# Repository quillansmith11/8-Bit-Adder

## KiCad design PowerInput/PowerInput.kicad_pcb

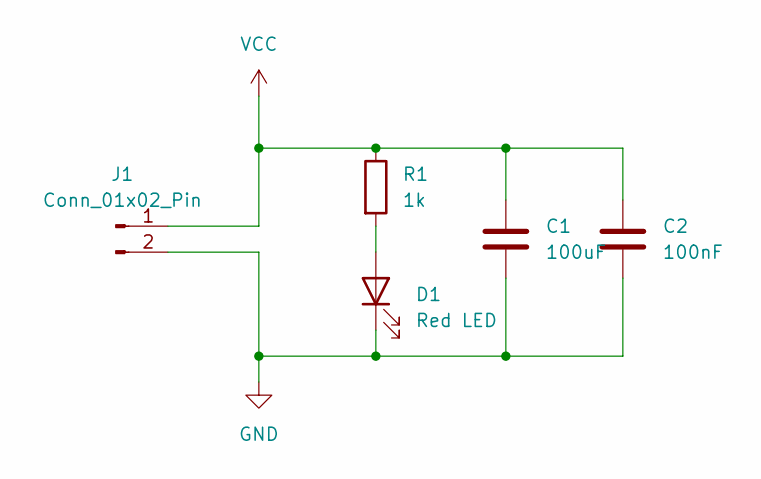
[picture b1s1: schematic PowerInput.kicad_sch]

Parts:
C1: 100uF; CP_Elec_10x10.5
C2: 100nF; C_0805_2012Metric
D1: Red LED; LED_0805_2012Metric
J1: Conn_01x02_Pin; BarrelJack_Kycon_KLDX-0202-xC_Horizontal
R1: 1k; R_0805_2012Metric

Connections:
GND: C1.2, C2.2, D1.1 (K), J1.2
unnamed: D1.2 (A), R1.2
VCC: C1.1, C2.1, J1.1, R1.1

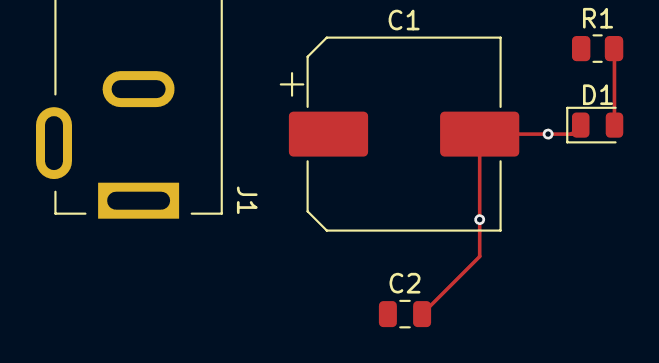
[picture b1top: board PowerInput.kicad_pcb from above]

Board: 2 copper layers, 5 parts (0 on the bottom side), 3 nets.

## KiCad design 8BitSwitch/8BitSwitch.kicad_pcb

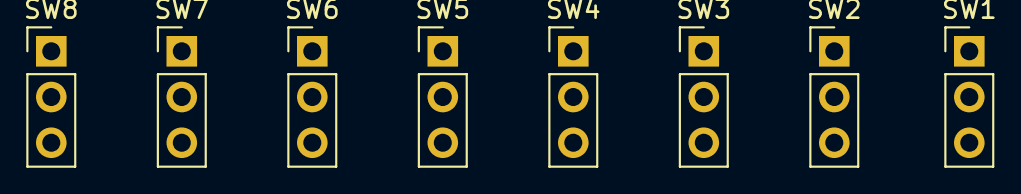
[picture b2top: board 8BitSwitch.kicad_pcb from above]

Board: 2 copper layers, 8 parts (0 on the bottom side), 2 nets, no tracks yet.

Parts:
SW1, SW2, SW3, SW4, SW5, SW6, SW7, SW8: SW_Nidec_CAS-120A1; PinHeader_1x03_P2.54mm_Vertical

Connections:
GND: SW1.3 (A), SW2.3 (A), SW3.3 (A), SW4.3 (A), SW5.3 (A), SW6.3 (A), SW7.3 (A), SW8.3 (A)
VCC: SW1.1 (C), SW2.1 (C), SW3.1 (C), SW4.1 (C), SW5.1 (C), SW6.1 (C), SW7.1 (C), SW8.1 (C)

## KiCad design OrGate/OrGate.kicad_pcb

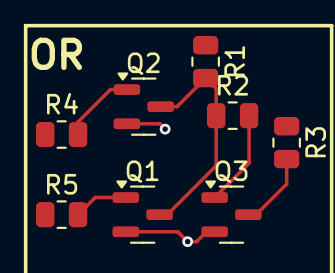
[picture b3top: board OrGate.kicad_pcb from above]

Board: 2 copper layers, 8 parts (0 on the bottom side), 7 nets.

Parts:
Q1, Q2, Q3: NPN Transistor; SOT-23
R1, R3: 2.7k; R_0805_2012Metric
R2: 39k; R_0805_2012Metric
R4, R5: 42k; R_0805_2012Metric

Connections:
/OUT: Q3.3 (C), R3.2
GND: Q1.2 (E), Q2.2 (E), Q3.2 (E)
unnamed: Q1.3 (C), Q2.3 (C), R1.2, R2.1
unnamed: Q1.1 (B), R5.2
unnamed: Q2.1 (B), R4.2
unnamed: Q3.1 (B), R2.2
VCC: R1.1, R3.1

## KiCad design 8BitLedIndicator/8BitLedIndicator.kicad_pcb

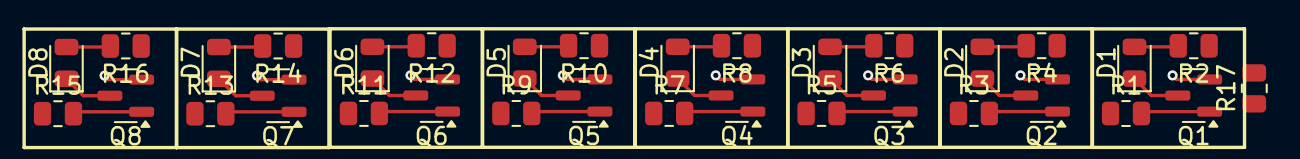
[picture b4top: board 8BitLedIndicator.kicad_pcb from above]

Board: 2 copper layers, 33 parts (0 on the bottom side), 26 nets.

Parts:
D1, D2, D3, D4, D5, D6, D7, D8: Red LED; LED_0805_2012Metric
Q1, Q2, Q3, Q4, Q5, Q6, Q7, Q8: NPN Transistor; SOT-23
R1, R3, R5, R7, R9, R11, R13, R15: 42k; R_0805_2012Metric
R2, R4, R6, R8, R10, R12, R14, R16: 200; R_0805_2012Metric
R17: R; R_0805_2012Metric

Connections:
GND: Q1.2 (E), Q2.2 (E), Q3.2 (E), Q4.2 (E), Q5.2 (E), Q6.2 (E), Q7.2 (E), Q8.2 (E)
unnamed: D1.2 (A), R2.2
unnamed: D1.1 (K), Q1.3 (C)
unnamed: D2.2 (A), R4.2
unnamed: D2.1 (K), Q2.3 (C)
unnamed: D3.2 (A), R6.2
unnamed: D3.1 (K), Q3.3 (C)
unnamed: D4.2 (A), R8.2
unnamed: D4.1 (K), Q4.3 (C)
unnamed: D5.2 (A), R10.2
unnamed: D5.1 (K), Q5.3 (C)
unnamed: D6.2 (A), R12.2
unnamed: D6.1 (K), Q6.3 (C)
unnamed: D7.2 (A), R14.2
unnamed: D7.1 (K), Q7.3 (C)
unnamed: D8.2 (A), R16.2
unnamed: D8.1 (K), Q8.3 (C)
unnamed: Q1.1 (B), R1.2
unnamed: Q2.1 (B), R3.2
unnamed: Q3.1 (B), R5.2
unnamed: Q4.1 (B), R7.2
unnamed: Q5.1 (B), R9.2
unnamed: Q6.1 (B), R11.2
unnamed: Q7.1 (B), R13.2
unnamed: Q8.1 (B), R15.2
VCC: R2.1, R4.1, R6.1, R8.1, R10.1, R12.1, R14.1, R16.1

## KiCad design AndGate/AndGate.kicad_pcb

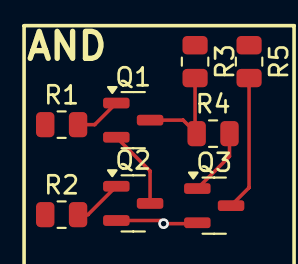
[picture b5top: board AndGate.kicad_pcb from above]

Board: 2 copper layers, 8 parts (0 on the bottom side), 8 nets.

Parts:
Q1, Q2, Q3: NPN Transistor; SOT-23
R1, R2: 42k; R_0805_2012Metric
R3: 2.1k; R_0805_2012Metric
R4: 39k; R_0805_2012Metric
R5: 2.7k; R_0805_2012Metric

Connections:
/OUT: Q3.3 (C), R5.2
GND: Q2.2 (E), Q3.2 (E)
unnamed: Q1.1 (B), R1.2
unnamed: Q1.3 (C), R3.2, R4.1
unnamed: Q1.2 (E), Q2.3 (C)
unnamed: Q2.1 (B), R2.2
unnamed: Q3.1 (B), R4.2
VCC: R3.1, R5.1

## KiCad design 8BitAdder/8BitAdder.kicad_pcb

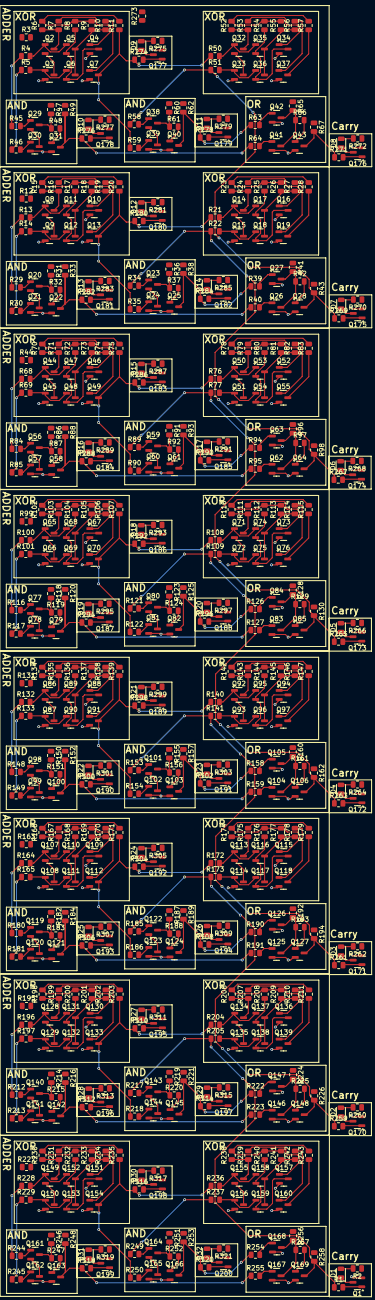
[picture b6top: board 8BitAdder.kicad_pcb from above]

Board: 2 copper layers, 553 parts (0 on the bottom side), 395 nets.

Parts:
D1, D2, D3, D4, D5, D6, D7, D8, D9, D10, D11, D12, D13, D14, D15, D16, D17, D18, D19, D20, D21, D22, D23, D24, D25, D26, D27, D28, D29, D30, D31, D32: Red LED; LED_0805_2012Metric
Q1, Q2, Q3, Q4, Q5, Q6, Q7, Q8, Q9, Q10, Q11, Q12, Q13, Q14, Q15, Q16, Q17, Q18, Q19, Q20, Q21, Q22, Q23, Q24, Q25, Q26, Q27, Q28, Q29, Q30, Q31, Q32, Q33, Q34, Q35, Q36, Q37, Q38, Q39, Q40, Q41, Q42, Q43, Q44, Q45, Q46, Q47, Q48, Q49, Q50, Q51, Q52, Q53, Q54, Q55, Q56, Q57, Q58, Q59, Q60, Q61, Q62, Q63, Q64, Q65, Q66, Q67, Q68, Q69, Q70, Q71, Q72, Q73, Q74, Q75, Q76, Q77, Q78, Q79, Q80, Q81, Q82, Q83, Q84, Q85, Q86, Q87, Q88, Q89, Q90, Q91, Q92, Q93, Q94, Q95, Q96, Q97, Q98, Q99, Q100, Q101, Q102, Q103, Q104, Q105, Q106, Q107, Q108, Q109, Q110, Q111, Q112, Q113, Q114, Q115, Q116, Q117, Q118, Q119, Q120, Q121, Q122, Q123, Q124, Q125, Q126, Q127, Q128, Q129, Q130, Q131, Q132, Q133, Q134, Q135, Q136, Q137, Q138, Q139, Q140, Q141, Q142, Q143, Q144, Q145, Q146, Q147, Q148, Q149, Q150, Q151, Q152, Q153, Q154, Q155, Q156, Q157, Q158, Q159, Q160, Q161, Q162, Q163, Q164, Q165, Q166, Q167, Q168, Q169, Q170, Q171, Q172, Q173, Q174, Q175, Q176, Q177, Q178, Q179, Q180, Q181, Q182, Q183, Q184, Q185, Q186, Q187, Q188, Q189, Q190, Q191, Q192, Q193, Q194, Q195, Q196, Q197, Q198, Q199, Q200: NPN Transistor; SOT-23
R1, R29, R30, R34, R35, R39, R40, R45, R46, R58, R59, R63, R64, R84, R85, R89, R90, R94, R95, R116, R117, R121, R122, R126, R127, R148, R149, R153, R154, R158, R159, R180, R181, R185, R186, R190, R191, R212, R213, R217, R218, R222, R223, R244, R245, R249, R250, R254, R255, R259, R261, R263, R265, R267, R269, R271, R274, R276, R278, R280, R282, R284, R286, R288, R290, R292, R294, R296, R298, R300, R302, R304, R306, R308, R310, R312, R314, R316, R318, R320: 42k; R_0805_2012Metric
R2, R260, R262, R264, R266, R268, R270, R272, R275, R277, R279, R281, R283, R285, R287, R289, R291, R293, R295, R297, R299, R301, R303, R305, R307, R309, R311, R313, R315, R317, R319, R321: 200; R_0805_2012Metric
R3, R12, R44, R99, R131, R163, R195, R227, R273: R; R_0805_2012Metric
R4, R5, R7, R13, R14, R16, R21, R22, R24, R50, R51, R53, R68, R69, R71, R76, R77, R79, R100, R101, R103, R108, R109, R111, R132, R133, R135, R140, R141, R143, R164, R165, R167, R172, R173, R175, R196, R197, R199, R204, R205, R207, R228, R229, R231, R236, R237, R239: 1k; R_0805_2012Metric
R6, R9, R15, R18, R23, R26, R31, R36, R47, R52, R55, R60, R70, R73, R78, R81, R86, R91, R102, R105, R110, R113, R118, R123, R134, R137, R142, R145, R150, R155, R166, R169, R174, R177, R182, R187, R198, R201, R206, R209, R214, R219, R230, R233, R238, R241, R246, R251: 2.1k; R_0805_2012Metric
R8, R11, R17, R20, R25, R28, R33, R38, R41, R43, R49, R54, R57, R62, R65, R67, R72, R75, R80, R83, R88, R93, R96, R98, R104, R107, R112, R115, R120, R125, R128, R130, R136, R139, R144, R147, R152, R157, R160, R162, R168, R171, R176, R179, R184, R189, R192, R194, R200, R203, R208, R211, R216, R221, R224, R226, R232, R235, R240, R243, R248, R253, R256, R258: 2.7k; R_0805_2012Metric
R10, R19, R27, R32, R37, R42, R48, R56, R61, R66, R74, R82, R87, R92, R97, R106, R114, R119, R124, R129, R138, R146, R151, R156, R161, R170, R178, R183, R188, R193, R202, R210, R215, R220, R225, R234, R242, R247, R252, R257: 39k; R_0805_2012Metric

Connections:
/A0: R228.1, R244.1
/A1: R196.1, R212.1
/A2: R164.1, R180.1
/A3: R132.1, R148.1
/A4: R100.1, R116.1
/A5: R68.1, R84.1
/A6: R13.1, R29.1
/A7: R4.1, R45.1
/Adder0/And Gate2/B: Q154.3 (C), R235.1, R236.1, R250.1, R316.1
/Adder0/And Gate2/OUT: Q166.3 (C), R253.2, R254.1, R320.1
/Adder0/And Gate3/OUT: Q163.3 (C), R248.2, R255.1, R318.1
/Adder0/XorGate1/Asig: Q155.1 (B), Q158.1 (B), R236.2
/Adder0/XorGate1/Bsig: Q156.1 (B), Q159.1 (B), R237.2
/Adder0/XorGate2/Asig: Q149.1 (B), Q152.1 (B), R228.2
/Adder0/XorGate2/Bsig: Q150.1 (B), Q153.1 (B), R229.2
/Adder1/And Gate2/B: Q133.3 (C), R203.1, R204.1, R218.1, R310.1
/Adder1/And Gate2/OUT: Q145.3 (C), R221.2, R222.1, R314.1
/Adder1/And Gate3/OUT: Q142.3 (C), R216.2, R223.1, R312.1
/Adder1/XorGate1/Asig: Q134.1 (B), Q137.1 (B), R204.2
/Adder1/XorGate1/Bsig: Q135.1 (B), Q138.1 (B), R205.2
/Adder1/XorGate2/Asig: Q128.1 (B), Q131.1 (B), R196.2
/Adder1/XorGate2/Bsig: Q129.1 (B), Q132.1 (B), R197.2
/Adder2/And Gate2/B: Q112.3 (C), R171.1, R172.1, R186.1, R304.1
/Adder2/And Gate2/OUT: Q124.3 (C), R189.2, R190.1, R308.1
/Adder2/And Gate3/OUT: Q121.3 (C), R184.2, R191.1, R306.1
/Adder2/XorGate1/Asig: Q113.1 (B), Q116.1 (B), R172.2
/Adder2/XorGate1/Bsig: Q114.1 (B), Q117.1 (B), R173.2
/Adder2/XorGate2/Asig: Q107.1 (B), Q110.1 (B), R164.2
/Adder2/XorGate2/Bsig: Q108.1 (B), Q111.1 (B), R165.2
/Adder3/And Gate2/B: Q91.3 (C), R139.1, R140.1, R154.1, R298.1
/Adder3/And Gate2/OUT: Q103.3 (C), R157.2, R158.1, R302.1
/Adder3/And Gate3/OUT: Q100.3 (C), R152.2, R159.1, R300.1
/Adder3/XorGate1/Asig: Q92.1 (B), Q95.1 (B), R140.2
/Adder3/XorGate1/Bsig: Q93.1 (B), Q96.1 (B), R141.2
/Adder3/XorGate2/Asig: Q86.1 (B), Q89.1 (B), R132.2
/Adder3/XorGate2/Bsig: Q87.1 (B), Q90.1 (B), R133.2
/Adder4/And Gate2/B: Q70.3 (C), R107.1, R108.1, R122.1, R292.1
/Adder4/And Gate2/OUT: Q82.3 (C), R125.2, R126.1, R296.1
/Adder4/And Gate3/OUT: Q79.3 (C), R120.2, R127.1, R294.1
/Adder4/Cout: Q85.3 (C), R77.1, R89.1, R130.2, R265.1
/Adder4/XorGate1/Asig: Q71.1 (B), Q74.1 (B), R108.2
/Adder4/XorGate1/Bsig: Q72.1 (B), Q75.1 (B), R109.2
/Adder4/XorGate2/Asig: Q65.1 (B), Q68.1 (B), R100.2
/Adder4/XorGate2/Bsig: Q66.1 (B), Q69.1 (B), R101.2
/Adder5/And Gate2/B: Q49.3 (C), R75.1, R76.1, R90.1, R286.1
/Adder5/And Gate2/OUT: Q61.3 (C), R93.2, R94.1, R290.1
/Adder5/And Gate3/OUT: Q58.3 (C), R88.2, R95.1, R288.1
/Adder5/XorGate1/Asig: Q50.1 (B), Q53.1 (B), R76.2
/Adder5/XorGate1/Bsig: Q51.1 (B), Q54.1 (B), R77.2
/Adder5/XorGate2/Asig: Q44.1 (B), Q47.1 (B), R68.2
/Adder5/XorGate2/Bsig: Q45.1 (B), Q48.1 (B), R69.2
/Adder6/And Gate2/B: Q13.3 (C), R20.1, R21.1, R35.1, R280.1
/Adder6/And Gate2/OUT: Q25.3 (C), R38.2, R39.1, R284.1
/Adder6/And Gate3/OUT: Q22.3 (C), R33.2, R40.1, R282.1
/Adder6/XorGate1/Asig: Q14.1 (B), Q17.1 (B), R21.2
/Adder6/XorGate1/Bsig: Q15.1 (B), Q18.1 (B), R22.2
/Adder6/XorGate2/Asig: Q8.1 (B), Q11.1 (B), R13.2
/Adder6/XorGate2/Bsig: Q9.1 (B), Q12.1 (B), R14.2
/Adder7/And Gate2/B: Q7.3 (C), R11.1, R50.1, R59.1, R274.1
/Adder7/And Gate2/OUT: Q40.3 (C), R62.2, R63.1, R278.1
/Adder7/And Gate3/OUT: Q31.3 (C), R49.2, R64.1, R276.1
/Adder7/XorGate1/Asig: Q32.1 (B), Q35.1 (B), R50.2
/Adder7/XorGate1/Bsig: Q33.1 (B), Q36.1 (B), R51.2
/Adder7/XorGate2/Asig: Q2.1 (B), Q5.1 (B), R4.2
/Adder7/XorGate2/Bsig: Q3.1 (B), Q6.1 (B), R5.2
/B0: R229.1, R245.1
/B1: R197.1, R213.1
/B2: R165.1, R181.1
/B3: R133.1, R149.1
/B4: R101.1, R117.1
/B5: R69.1, R85.1
/B6: R14.1, R30.1
/B7: R5.1, R46.1
/Cin: R237.1, R249.1
/Cout0: Q169.3 (C), R1.1, R205.1, R217.1, R258.2
/Cout1: Q148.3 (C), R173.1, R185.1, R226.2, R259.1
/Cout2: Q127.3 (C), R141.1, R153.1, R194.2, R261.1
/Cout3: Q106.3 (C), R109.1, R121.1, R162.2, R263.1
/Cout5: Q64.3 (C), R22.1, R34.1, R98.2, R267.1
/Cout6: Q28.3 (C), R43.2, R51.1, R58.1, R269.1
/Cout7: Q43.3 (C), R67.2, R271.1
/SUM0: Q160.3 (C), R243.1
/SUM1: Q139.3 (C), R211.1
/SUM2: Q118.3 (C), R179.1
/SUM3: Q97.3 (C), R147.1
/SUM4: Q76.3 (C), R115.1
/SUM5: Q55.3 (C), R83.1
/SUM6: Q19.3 (C), R28.1
/SUM7: Q37.3 (C), R57.1
GND: Q1.2 (E), Q3.2 (E), Q4.2 (E), Q7.2 (E), Q9.2 (E), Q10.2 (E), Q13.2 (E), Q15.2 (E), Q16.2 (E), Q19.2 (E), Q21.2 (E), Q22.2 (E), Q24.2 (E), Q25.2 (E), Q26.2 (E), Q27.2 (E), Q28.2 (E), Q30.2 (E), Q31.2 (E), Q33.2 (E), Q34.2 (E), Q37.2 (E), Q39.2 (E), Q40.2 (E), Q41.2 (E), Q42.2 (E), Q43.2 (E), Q45.2 (E), Q46.2 (E), Q49.2 (E), Q51.2 (E), Q52.2 (E), Q55.2 (E), Q57.2 (E), Q58.2 (E), Q60.2 (E), Q61.2 (E), Q62.2 (E), Q63.2 (E), Q64.2 (E), Q66.2 (E), Q67.2 (E), Q70.2 (E), Q72.2 (E), Q73.2 (E), Q76.2 (E), Q78.2 (E), Q79.2 (E), Q81.2 (E), Q82.2 (E), Q83.2 (E), Q84.2 (E), Q85.2 (E), Q87.2 (E), Q88.2 (E), Q91.2 (E), Q93.2 (E), Q94.2 (E), Q97.2 (E), Q99.2 (E), Q100.2 (E), Q102.2 (E), Q103.2 (E), Q104.2 (E), Q105.2 (E), Q106.2 (E), Q108.2 (E), Q109.2 (E), Q112.2 (E), Q114.2 (E), Q115.2 (E), Q118.2 (E), Q120.2 (E), Q121.2 (E), Q123.2 (E), Q124.2 (E), Q125.2 (E), Q126.2 (E), Q127.2 (E), Q129.2 (E), Q130.2 (E), Q133.2 (E), Q135.2 (E), Q136.2 (E), Q139.2 (E), Q141.2 (E), Q142.2 (E), Q144.2 (E), Q145.2 (E), Q146.2 (E), Q147.2 (E), Q148.2 (E), Q150.2 (E), Q151.2 (E), Q154.2 (E), Q156.2 (E), Q157.2 (E), Q160.2 (E), Q162.2 (E), Q163.2 (E), Q165.2 (E), Q166.2 (E), Q167.2 (E), Q168.2 (E), Q169.2 (E), Q170.2 (E), Q171.2 (E), Q172.2 (E), Q173.2 (E), Q174.2 (E), Q175.2 (E), Q176.2 (E), Q177.2 (E), Q178.2 (E), Q179.2 (E), Q180.2 (E), Q181.2 (E), Q182.2 (E), Q183.2 (E), Q184.2 (E), Q185.2 (E), Q186.2 (E), Q187.2 (E), Q188.2 (E), Q189.2 (E), Q190.2 (E), Q191.2 (E), Q192.2 (E), Q193.2 (E), Q194.2 (E), Q195.2 (E), Q196.2 (E), Q197.2 (E), Q198.2 (E), Q199.2 (E), Q200.2 (E)
unnamed: D1.2 (A), R2.2
unnamed: D1.1 (K), Q1.3 (C)
unnamed: D2.2 (A), R260.2
unnamed: D2.1 (K), Q170.3 (C)
unnamed: D3.2 (A), R262.2
unnamed: D3.1 (K), Q171.3 (C)
unnamed: D4.2 (A), R264.2
unnamed: D4.1 (K), Q172.3 (C)
unnamed: D5.2 (A), R266.2
unnamed: D5.1 (K), Q173.3 (C)
unnamed: D6.2 (A), R268.2
unnamed: D6.1 (K), Q174.3 (C)
unnamed: D7.2 (A), R270.2
unnamed: D7.1 (K), Q175.3 (C)
unnamed: D8.2 (A), R272.2
unnamed: D8.1 (K), Q176.3 (C)
unnamed: D9.2 (A), R275.2
unnamed: D9.1 (K), Q177.3 (C)
unnamed: D10.2 (A), R277.2
unnamed: D10.1 (K), Q178.3 (C)
unnamed: D11.2 (A), R279.2
unnamed: D11.1 (K), Q179.3 (C)
unnamed: D12.2 (A), R281.2
unnamed: D12.1 (K), Q180.3 (C)
unnamed: D13.2 (A), R283.2
unnamed: D13.1 (K), Q181.3 (C)
unnamed: D14.2 (A), R285.2
unnamed: D14.1 (K), Q182.3 (C)
unnamed: D15.2 (A), R287.2
unnamed: D15.1 (K), Q183.3 (C)
unnamed: D16.2 (A), R289.2
unnamed: D16.1 (K), Q184.3 (C)
unnamed: D17.2 (A), R291.2
unnamed: D17.1 (K), Q185.3 (C)
unnamed: D18.2 (A), R293.2
unnamed: D18.1 (K), Q186.3 (C)
unnamed: D19.2 (A), R295.2
unnamed: D19.1 (K), Q187.3 (C)
unnamed: D20.2 (A), R297.2
unnamed: D20.1 (K), Q188.3 (C)
unnamed: D21.2 (A), R299.2
unnamed: D21.1 (K), Q189.3 (C)
unnamed: D22.2 (A), R301.2
unnamed: D22.1 (K), Q190.3 (C)
unnamed: D23.2 (A), R303.2
unnamed: D23.1 (K), Q191.3 (C)
unnamed: D24.2 (A), R305.2
unnamed: D24.1 (K), Q192.3 (C)
unnamed: D25.2 (A), R307.2
unnamed: D25.1 (K), Q193.3 (C)
unnamed: D26.2 (A), R309.2
unnamed: D26.1 (K), Q194.3 (C)
unnamed: D27.2 (A), R311.2
unnamed: D27.1 (K), Q195.3 (C)
unnamed: D28.2 (A), R313.2
unnamed: D28.1 (K), Q196.3 (C)
unnamed: D29.2 (A), R315.2
unnamed: D29.1 (K), Q197.3 (C)
unnamed: D30.2 (A), R317.2
unnamed: D30.1 (K), Q198.3 (C)
unnamed: D31.2 (A), R319.2
unnamed: D31.1 (K), Q199.3 (C)
unnamed: D32.2 (A), R321.2
unnamed: D32.1 (K), Q200.3 (C)
unnamed: Q1.1 (B), R1.2
unnamed: Q2.3 (C), R6.1, R7.1
unnamed: Q2.2 (E), Q3.3 (C)
unnamed: Q4.1 (B), R7.2
unnamed: Q4.3 (C), Q5.2 (E), Q6.2 (E), R8.1
unnamed: Q5.3 (C), Q6.3 (C), R9.1, R10.1
unnamed: Q7.1 (B), R10.2
unnamed: Q8.3 (C), R15.1, R16.1
unnamed: Q8.2 (E), Q9.3 (C)
unnamed: Q10.1 (B), R16.2
unnamed: Q10.3 (C), Q11.2 (E), Q12.2 (E), R17.1
unnamed: Q11.3 (C), Q12.3 (C), R18.1, R19.1
unnamed: Q13.1 (B), R19.2
unnamed: Q14.3 (C), R23.1, R24.1
unnamed: Q14.2 (E), Q15.3 (C)
unnamed: Q16.1 (B), R24.2
unnamed: Q16.3 (C), Q17.2 (E), Q18.2 (E), R25.1
unnamed: Q17.3 (C), Q18.3 (C), R26.1, R27.1
unnamed: Q19.1 (B), R27.2
unnamed: Q20.1 (B), R29.2
unnamed: Q20.3 (C), R31.2, R32.1
unnamed: Q20.2 (E), Q21.3 (C)
unnamed: Q21.1 (B), R30.2
unnamed: Q22.1 (B), R32.2
unnamed: Q23.1 (B), R34.2
unnamed: Q23.3 (C), R36.2, R37.1
unnamed: Q23.2 (E), Q24.3 (C)
unnamed: Q24.1 (B), R35.2
unnamed: Q25.1 (B), R37.2
unnamed: Q26.1 (B), R40.2
unnamed: Q26.3 (C), Q27.3 (C), R41.2, R42.1
unnamed: Q27.1 (B), R39.2
unnamed: Q28.1 (B), R42.2
unnamed: Q29.1 (B), R45.2
unnamed: Q29.3 (C), R47.2, R48.1
unnamed: Q29.2 (E), Q30.3 (C)
unnamed: Q30.1 (B), R46.2
unnamed: Q31.1 (B), R48.2
unnamed: Q32.3 (C), R52.1, R53.1
unnamed: Q32.2 (E), Q33.3 (C)
unnamed: Q34.1 (B), R53.2
unnamed: Q34.3 (C), Q35.2 (E), Q36.2 (E), R54.1
unnamed: Q35.3 (C), Q36.3 (C), R55.1, R56.1
unnamed: Q37.1 (B), R56.2
unnamed: Q38.1 (B), R58.2
unnamed: Q38.3 (C), R60.2, R61.1
unnamed: Q38.2 (E), Q39.3 (C)
unnamed: Q39.1 (B), R59.2
unnamed: Q40.1 (B), R61.2
unnamed: Q41.1 (B), R64.2
unnamed: Q41.3 (C), Q42.3 (C), R65.2, R66.1
unnamed: Q42.1 (B), R63.2
unnamed: Q43.1 (B), R66.2
unnamed: Q44.3 (C), R70.1, R71.1
unnamed: Q44.2 (E), Q45.3 (C)
unnamed: Q46.1 (B), R71.2
unnamed: Q46.3 (C), Q47.2 (E), Q48.2 (E), R72.1
unnamed: Q47.3 (C), Q48.3 (C), R73.1, R74.1
unnamed: Q49.1 (B), R74.2
unnamed: Q50.3 (C), R78.1, R79.1
unnamed: Q50.2 (E), Q51.3 (C)
unnamed: Q52.1 (B), R79.2
unnamed: Q52.3 (C), Q53.2 (E), Q54.2 (E), R80.1
unnamed: Q53.3 (C), Q54.3 (C), R81.1, R82.1
unnamed: Q55.1 (B), R82.2
unnamed: Q56.1 (B), R84.2
unnamed: Q56.3 (C), R86.2, R87.1
unnamed: Q56.2 (E), Q57.3 (C)
unnamed: Q57.1 (B), R85.2
unnamed: Q58.1 (B), R87.2
unnamed: Q59.1 (B), R89.2
unnamed: Q59.3 (C), R91.2, R92.1
unnamed: Q59.2 (E), Q60.3 (C)
unnamed: Q60.1 (B), R90.2
unnamed: Q61.1 (B), R92.2
unnamed: Q62.1 (B), R95.2
unnamed: Q62.3 (C), Q63.3 (C), R96.2, R97.1
unnamed: Q63.1 (B), R94.2
unnamed: Q64.1 (B), R97.2
unnamed: Q65.3 (C), R102.1, R103.1
unnamed: Q65.2 (E), Q66.3 (C)
unnamed: Q67.1 (B), R103.2
unnamed: Q67.3 (C), Q68.2 (E), Q69.2 (E), R104.1
unnamed: Q68.3 (C), Q69.3 (C), R105.1, R106.1
unnamed: Q70.1 (B), R106.2
unnamed: Q71.3 (C), R110.1, R111.1
unnamed: Q71.2 (E), Q72.3 (C)
unnamed: Q73.1 (B), R111.2
unnamed: Q73.3 (C), Q74.2 (E), Q75.2 (E), R112.1
unnamed: Q74.3 (C), Q75.3 (C), R113.1, R114.1
unnamed: Q76.1 (B), R114.2
unnamed: Q77.1 (B), R116.2
unnamed: Q77.3 (C), R118.2, R119.1
unnamed: Q77.2 (E), Q78.3 (C)
unnamed: Q78.1 (B), R117.2
unnamed: Q79.1 (B), R119.2
unnamed: Q80.1 (B), R121.2
unnamed: Q80.3 (C), R123.2, R124.1
unnamed: Q80.2 (E), Q81.3 (C)
unnamed: Q81.1 (B), R122.2
unnamed: Q82.1 (B), R124.2
unnamed: Q83.1 (B), R127.2
unnamed: Q83.3 (C), Q84.3 (C), R128.2, R129.1
unnamed: Q84.1 (B), R126.2
unnamed: Q85.1 (B), R129.2
unnamed: Q86.3 (C), R134.1, R135.1
unnamed: Q86.2 (E), Q87.3 (C)
unnamed: Q88.1 (B), R135.2
unnamed: Q88.3 (C), Q89.2 (E), Q90.2 (E), R136.1
unnamed: Q89.3 (C), Q90.3 (C), R137.1, R138.1
unnamed: Q91.1 (B), R138.2
unnamed: Q92.3 (C), R142.1, R143.1
unnamed: Q92.2 (E), Q93.3 (C)
unnamed: Q94.1 (B), R143.2
unnamed: Q94.3 (C), Q95.2 (E), Q96.2 (E), R144.1
unnamed: Q95.3 (C), Q96.3 (C), R145.1, R146.1
unnamed: Q97.1 (B), R146.2
unnamed: Q98.1 (B), R148.2
unnamed: Q98.3 (C), R150.2, R151.1
unnamed: Q98.2 (E), Q99.3 (C)
unnamed: Q99.1 (B), R149.2
unnamed: Q100.1 (B), R151.2
unnamed: Q101.1 (B), R153.2
unnamed: Q101.3 (C), R155.2, R156.1
unnamed: Q101.2 (E), Q102.3 (C)
unnamed: Q102.1 (B), R154.2
unnamed: Q103.1 (B), R156.2
unnamed: Q104.1 (B), R159.2
unnamed: Q104.3 (C), Q105.3 (C), R160.2, R161.1
unnamed: Q105.1 (B), R158.2
unnamed: Q106.1 (B), R161.2
unnamed: Q107.3 (C), R166.1, R167.1
unnamed: Q107.2 (E), Q108.3 (C)
unnamed: Q109.1 (B), R167.2
unnamed: Q109.3 (C), Q110.2 (E), Q111.2 (E), R168.1
unnamed: Q110.3 (C), Q111.3 (C), R169.1, R170.1
unnamed: Q112.1 (B), R170.2
unnamed: Q113.3 (C), R174.1, R175.1
unnamed: Q113.2 (E), Q114.3 (C)
unnamed: Q115.1 (B), R175.2
unnamed: Q115.3 (C), Q116.2 (E), Q117.2 (E), R176.1
unnamed: Q116.3 (C), Q117.3 (C), R177.1, R178.1
unnamed: Q118.1 (B), R178.2
unnamed: Q119.1 (B), R180.2
unnamed: Q119.3 (C), R182.2, R183.1
unnamed: Q119.2 (E), Q120.3 (C)
unnamed: Q120.1 (B), R181.2
unnamed: Q121.1 (B), R183.2
unnamed: Q122.1 (B), R185.2
unnamed: Q122.3 (C), R187.2, R188.1
unnamed: Q122.2 (E), Q123.3 (C)
unnamed: Q123.1 (B), R186.2
unnamed: Q124.1 (B), R188.2
unnamed: Q125.1 (B), R191.2
unnamed: Q125.3 (C), Q126.3 (C), R192.2, R193.1
unnamed: Q126.1 (B), R190.2
unnamed: Q127.1 (B), R193.2
unnamed: Q128.3 (C), R198.1, R199.1
unnamed: Q128.2 (E), Q129.3 (C)
unnamed: Q130.1 (B), R199.2
unnamed: Q130.3 (C), Q131.2 (E), Q132.2 (E), R200.1
unnamed: Q131.3 (C), Q132.3 (C), R201.1, R202.1
unnamed: Q133.1 (B), R202.2
unnamed: Q134.3 (C), R206.1, R207.1
unnamed: Q134.2 (E), Q135.3 (C)
unnamed: Q136.1 (B), R207.2
unnamed: Q136.3 (C), Q137.2 (E), Q138.2 (E), R208.1
unnamed: Q137.3 (C), Q138.3 (C), R209.1, R210.1
unnamed: Q139.1 (B), R210.2
unnamed: Q140.1 (B), R212.2
unnamed: Q140.3 (C), R214.2, R215.1
unnamed: Q140.2 (E), Q141.3 (C)
unnamed: Q141.1 (B), R213.2
unnamed: Q142.1 (B), R215.2
unnamed: Q143.1 (B), R217.2
unnamed: Q143.3 (C), R219.2, R220.1
unnamed: Q143.2 (E), Q144.3 (C)
unnamed: Q144.1 (B), R218.2
unnamed: Q145.1 (B), R220.2
unnamed: Q146.1 (B), R223.2
unnamed: Q146.3 (C), Q147.3 (C), R224.2, R225.1
unnamed: Q147.1 (B), R222.2
unnamed: Q148.1 (B), R225.2
unnamed: Q149.3 (C), R230.1, R231.1
unnamed: Q149.2 (E), Q150.3 (C)
unnamed: Q151.1 (B), R231.2
unnamed: Q151.3 (C), Q152.2 (E), Q153.2 (E), R232.1
unnamed: Q152.3 (C), Q153.3 (C), R233.1, R234.1
unnamed: Q154.1 (B), R234.2
unnamed: Q155.3 (C), R238.1, R239.1
unnamed: Q155.2 (E), Q156.3 (C)
unnamed: Q157.1 (B), R239.2
unnamed: Q157.3 (C), Q158.2 (E), Q159.2 (E), R240.1
unnamed: Q158.3 (C), Q159.3 (C), R241.1, R242.1
unnamed: Q160.1 (B), R242.2
unnamed: Q161.1 (B), R244.2
unnamed: Q161.3 (C), R246.2, R247.1
unnamed: Q161.2 (E), Q162.3 (C)
unnamed: Q162.1 (B), R245.2
unnamed: Q163.1 (B), R247.2
unnamed: Q164.1 (B), R249.2
unnamed: Q164.3 (C), R251.2, R252.1
unnamed: Q164.2 (E), Q165.3 (C)
unnamed: Q165.1 (B), R250.2
unnamed: Q166.1 (B), R252.2
unnamed: Q167.1 (B), R255.2
unnamed: Q167.3 (C), Q168.3 (C), R256.2, R257.1
unnamed: Q168.1 (B), R254.2
unnamed: Q169.1 (B), R257.2
unnamed: Q170.1 (B), R259.2
unnamed: Q171.1 (B), R261.2
unnamed: Q172.1 (B), R263.2
unnamed: Q173.1 (B), R265.2
unnamed: Q174.1 (B), R267.2
unnamed: Q175.1 (B), R269.2
unnamed: Q176.1 (B), R271.2
unnamed: Q177.1 (B), R274.2
unnamed: Q178.1 (B), R276.2
unnamed: Q179.1 (B), R278.2
unnamed: Q180.1 (B), R280.2
unnamed: Q181.1 (B), R282.2
unnamed: Q182.1 (B), R284.2
unnamed: Q183.1 (B), R286.2
unnamed: Q184.1 (B), R288.2
unnamed: Q185.1 (B), R290.2
unnamed: Q186.1 (B), R292.2
unnamed: Q187.1 (B), R294.2
unnamed: Q188.1 (B), R296.2
unnamed: Q189.1 (B), R298.2
unnamed: Q190.1 (B), R300.2
unnamed: Q191.1 (B), R302.2
unnamed: Q192.1 (B), R304.2
unnamed: Q193.1 (B), R306.2
unnamed: Q194.1 (B), R308.2
unnamed: Q195.1 (B), R310.2
unnamed: Q196.1 (B), R312.2
unnamed: Q197.1 (B), R314.2
unnamed: Q198.1 (B), R316.2
unnamed: Q199.1 (B), R318.2
unnamed: Q200.1 (B), R320.2
VCC: R2.1, R6.2, R8.2, R9.2, R11.2, R15.2, R17.2, R18.2, R20.2, R23.2, R25.2, R26.2, R28.2, R31.1, R33.1, R36.1, R38.1, R41.1, R43.1, R47.1, R49.1, R52.2, R54.2, R55.2, R57.2, R60.1, R62.1, R65.1, R67.1, R70.2, R72.2, R73.2, R75.2, R78.2, R80.2, R81.2, R83.2, R86.1, R88.1, R91.1, R93.1, R96.1, R98.1, R102.2, R104.2, R105.2, R107.2, R110.2, R112.2, R113.2, R115.2, R118.1, R120.1, R123.1, R125.1, R128.1, R130.1, R134.2, R136.2, R137.2, R139.2, R142.2, R144.2, R145.2, R147.2, R150.1, R152.1, R155.1, R157.1, R160.1, R162.1, R166.2, R168.2, R169.2, R171.2, R174.2, R176.2, R177.2, R179.2, R182.1, R184.1, R187.1, R189.1, R192.1, R194.1, R198.2, R200.2, R201.2, R203.2, R206.2, R208.2, R209.2, R211.2, R214.1, R216.1, R219.1, R221.1, R224.1, R226.1, R230.2, R232.2, R233.2, R235.2, R238.2, R240.2, R241.2, R243.2, R246.1, R248.1, R251.1, R253.1, R256.1, R258.1, R260.1, R262.1, R264.1, R266.1, R268.1, R270.1, R272.1, R275.1, R277.1, R279.1, R281.1, R283.1, R285.1, R287.1, R289.1, R291.1, R293.1, R295.1, R297.1, R299.1, R301.1, R303.1, R305.1, R307.1, R309.1, R311.1, R313.1, R315.1, R317.1, R319.1, R321.1

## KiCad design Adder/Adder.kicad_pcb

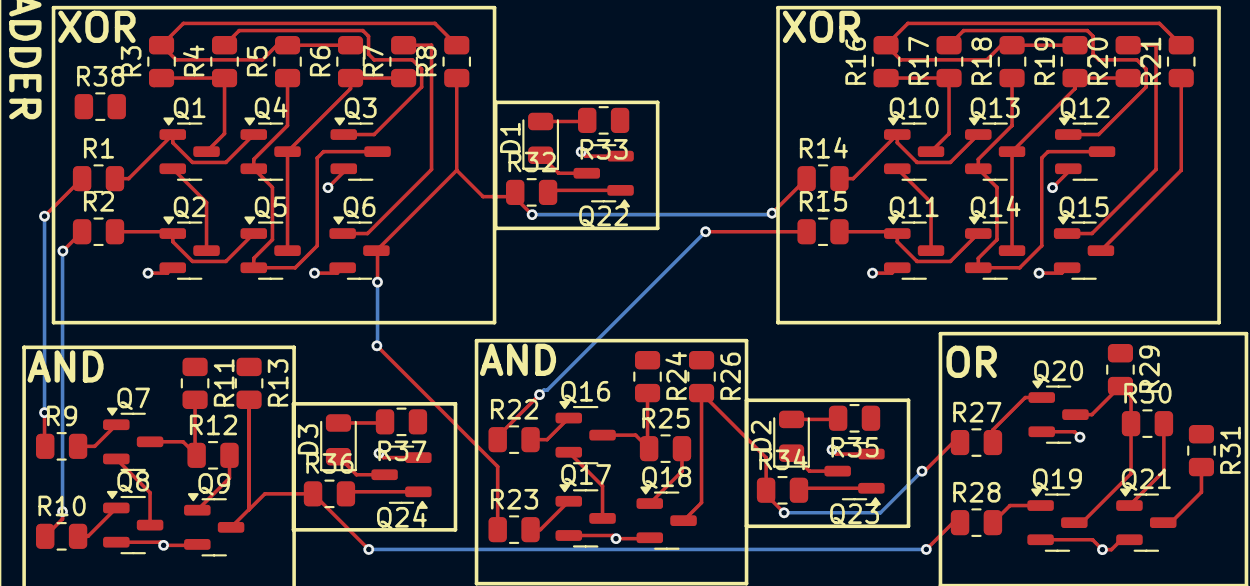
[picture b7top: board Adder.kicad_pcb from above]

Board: 2 copper layers, 65 parts (0 on the bottom side), 49 nets.

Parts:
D1, D2, D3: Red LED; LED_0805_2012Metric
Q1, Q2, Q3, Q4, Q5, Q6, Q7, Q8, Q9, Q10, Q11, Q12, Q13, Q14, Q15, Q16, Q17, Q18, Q19, Q20, Q21, Q22, Q23, Q24: NPN Transistor; SOT-23
R1, R2, R4, R14, R15, R17: 1k; R_0805_2012Metric
R3, R6, R11, R16, R19, R24: 2.1k; R_0805_2012Metric
R5, R8, R13, R18, R21, R26, R29, R31: 2.7k; R_0805_2012Metric
R7, R12, R20, R25, R30: 39k; R_0805_2012Metric
R9, R10, R22, R23, R27, R28, R32, R34, R36: 42k; R_0805_2012Metric
R33, R35, R37: 200; R_0805_2012Metric
R38: R; R_0805_2012Metric

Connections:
/A: R1.1, R9.1
/And Gate2/B: Q6.3 (C), R8.1, R14.1, R23.1, R32.1
/And Gate2/OUT: Q18.3 (C), R26.2, R27.1, R34.1
/And Gate3/OUT: Q9.3 (C), R13.2, R28.1, R36.1
/B: R2.1, R10.1
/Cin: R15.1, R22.1
/Cout: Q21.3 (C), R31.2
/SUM: Q15.3 (C), R21.1
/XorGate1/Asig: Q10.1 (B), Q13.1 (B), R14.2
/XorGate1/Bsig: Q11.1 (B), Q14.1 (B), R15.2
/XorGate2/Asig: Q1.1 (B), Q4.1 (B), R1.2
/XorGate2/Bsig: Q2.1 (B), Q5.1 (B), R2.2
GND: Q2.2 (E), Q3.2 (E), Q6.2 (E), Q8.2 (E), Q9.2 (E), Q11.2 (E), Q12.2 (E), Q15.2 (E), Q17.2 (E), Q18.2 (E), Q19.2 (E), Q20.2 (E), Q21.2 (E), Q22.2 (E), Q23.2 (E), Q24.2 (E)
unnamed: D1.2 (A), R33.2
unnamed: D1.1 (K), Q22.3 (C)
unnamed: D2.2 (A), R35.2
unnamed: D2.1 (K), Q23.3 (C)
unnamed: D3.2 (A), R37.2
unnamed: D3.1 (K), Q24.3 (C)
unnamed: Q1.3 (C), R3.1, R4.1
unnamed: Q1.2 (E), Q2.3 (C)
unnamed: Q3.1 (B), R4.2
unnamed: Q3.3 (C), Q4.2 (E), Q5.2 (E), R5.1
unnamed: Q4.3 (C), Q5.3 (C), R6.1, R7.1
unnamed: Q6.1 (B), R7.2
unnamed: Q7.1 (B), R9.2
unnamed: Q7.3 (C), R11.2, R12.1
unnamed: Q7.2 (E), Q8.3 (C)
unnamed: Q8.1 (B), R10.2
unnamed: Q9.1 (B), R12.2
unnamed: Q10.3 (C), R16.1, R17.1
unnamed: Q10.2 (E), Q11.3 (C)
unnamed: Q12.1 (B), R17.2
unnamed: Q12.3 (C), Q13.2 (E), Q14.2 (E), R18.1
unnamed: Q13.3 (C), Q14.3 (C), R19.1, R20.1
unnamed: Q15.1 (B), R20.2
unnamed: Q16.1 (B), R22.2
unnamed: Q16.3 (C), R24.2, R25.1
unnamed: Q16.2 (E), Q17.3 (C)
unnamed: Q17.1 (B), R23.2
unnamed: Q18.1 (B), R25.2
unnamed: Q19.1 (B), R28.2
unnamed: Q19.3 (C), Q20.3 (C), R29.2, R30.1
unnamed: Q20.1 (B), R27.2
unnamed: Q21.1 (B), R30.2
unnamed: Q22.1 (B), R32.2
unnamed: Q23.1 (B), R34.2
unnamed: Q24.1 (B), R36.2
VCC: R3.2, R5.2, R6.2, R8.2, R11.1, R13.1, R16.2, R18.2, R19.2, R21.2, R24.1, R26.1, R29.1, R31.1, R33.1, R35.1, R37.1

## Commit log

2024-10-17 Initial KiCad commit
